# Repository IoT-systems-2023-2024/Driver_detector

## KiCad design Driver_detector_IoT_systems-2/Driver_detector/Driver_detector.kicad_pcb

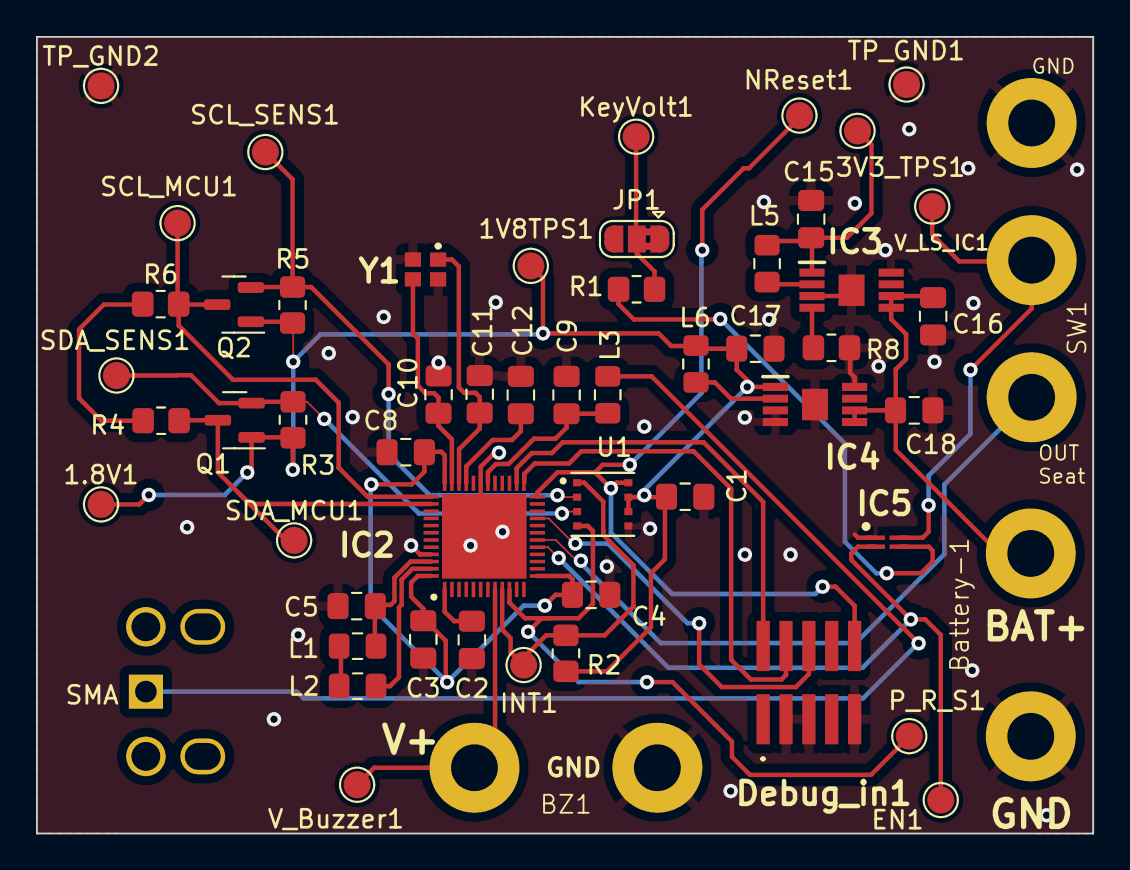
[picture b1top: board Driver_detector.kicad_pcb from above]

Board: 2 copper layers, 58.7 x 44.3 mm, 56 parts (0 on the bottom side), 34 nets.

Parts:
1.8V1, 1V8TPS1, 3V3_TPS1: TestPoint; TestPoint_Pad_D1.5mm
AE1: Antenna; SMA-connector
BZ1: Buzzer; Battery_pad
Battery-1: Battery+; Battery_pad
C1: 0.1 nF; C_0805_2012Metric_Pad1.18x1.45mm_HandSolder
C2, C4, C8: 100nF; C_0805_2012Metric_Pad1.18x1.45mm_HandSolder
C3, C16, C18: 4.7uF; C_0805_2012Metric_Pad1.18x1.45mm_HandSolder
C5: 1uF; C_0805_2012Metric_Pad1.18x1.45mm_HandSolder
C9: 0.8pF; C_0805_2012Metric_Pad1.18x1.45mm_HandSolder
C10, C11: 12pF; C_0805_2012Metric_Pad1.18x1.45mm_HandSolder
C12: 100pF; C_0805_2012Metric_Pad1.18x1.45mm_HandSolder
C15, C17: 10uF; C_0805_2012Metric_Pad1.18x1.45mm_HandSolder
Debug_in1: Pin header 2x5, 1.27mm; FTSH10501LDVK
EN1: TestPoint; TestPoint_Pad_D1.5mm
IC2: NRF52832-QFAA-G-R7; QFN40P600X600X95-49N
IC3, IC4: TPS62842DGR; SOP65P490X110-9N
IC5: LS0504EDD12; SON50P160X120X60-4N
INT1: TestPoint; TestPoint_Pad_D1.5mm
JP1: Jumper_2_Bridged; SolderJumper-3_P1.3mm_Bridged2Bar12_RoundedPad1.0x1.5mm
KeyVolt1: TestPoint; TestPoint_Pad_D1.5mm
L1: 15nH; L_0805_2012Metric_Pad1.15x1.40mm_HandSolder
L2: 10uH; L_0805_2012Metric_Pad1.15x1.40mm_HandSolder
L3: 3.9nH; L_0805_2012Metric_Pad1.15x1.40mm_HandSolder
L5, L6: 2.2uH; L_0805_2012Metric_Pad1.15x1.40mm_HandSolder
NReset1: TestPoint; TestPoint_Pad_D1.5mm
P_R_S1: TestPoint; TestPoint_Pad_D1.5mm
Q1, Q2: BSS138; SOT-23
R1: OR; R_0805_2012Metric_Pad1.20x1.40mm_HandSolder
R2, R3, R4, R5, R6: 10k; R_0805_2012Metric_Pad1.20x1.40mm_HandSolder
R8: 52.3kOhm; R_0805_2012Metric_Pad1.20x1.40mm_HandSolder
SCL_MCU1: TestPoint; TestPoint_Pad_D1.5mm
SCL_SENS1: TestPoint; TestPoint_Pad_D1.5mm
SDA_MCU1: TestPoint; TestPoint_Pad_D1.5mm
SDA_SENS1: TestPoint; TestPoint_Pad_D1.5mm
SW1: SW_SPDT; Footprint_switch
TP_GND1, TP_GND2: TestPoint; TestPoint_Pad_D1.5mm
U1: CH-101; XDCR_CH-101
V_Buzzer1: TestPoint; TestPoint_Pad_D1.5mm
V_LS_IC1: TestPoint; TestPoint_Pad_D1.5mm
Y1: CX2016DB32000D0FLJCC

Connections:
+1V8: 1.8V1.1, 1V8TPS1.1, C1.2, C17.1, IC4.1 (VOS), L6.1, Q1.1 (G), Q2.1 (G), R2.1, R3.1, R5.1, U1.6 (VDD), U1.7 (AVDD)
+3.3V: R4.1, R6.1
Battery +: Battery-1.2, C16.1, C18.1, IC3.5 (EN), IC3.6 (VIN), IC4.5 (EN), IC4.6 (VIN)
EN: EN1.1, IC2.17 (P0.14/TRACEDATA[3]), IC5.2 (EN)
GND: BZ1.2 (+), Battery-1.1, C1.1, C2.1, C3.2, C4.2, C5.2, C8.2, C9.2, C10.2, C11.1, C12.1, C15.2, C16.2, C17.2, C18.2, Debug_in1.3, Debug_in1.5, Debug_in1.9, IC2.31 (VSS_1), IC2.45 (VSS_2), IC2.49 (EP), IC3.3 (MODE), IC3.8 (GND), IC3.9 (EP), IC4.3 (MODE), IC4.4 (VSET), IC4.8 (GND), IC4.9 (EP), IC5.1 (GND), R8.2, SW1.1 (A), TP_GND1.1, TP_GND2.1, U1.5 (VSS), Y1.2 (GND_1), Y1.4 (GND_2)
INT: IC2.9 (P0.07), INT1.1, R2.2, U1.1 (INT)
NRESET: Debug_in1.10, IC2.24 (P0.21/NRESET), NReset1.1, U1.8 (~RESET)
unnamed: AE1.1 (A), L3.2
unnamed: C9.1, IC2.30 (ANT), L3.1
unnamed: IC2.47 (DCC), L2.2
unnamed: C2.2, IC2.1 (DEC1)
unnamed: C12.2, IC2.33 (DEC3)
unnamed: C5.1, IC2.46 (DEC4), L1.1
unnamed: C11.2, IC2.34 (XC1), Y1.1 (HOT_1)
unnamed: C10.1, IC2.35 (XC2), Y1.3 (HOT_2)
unnamed: IC3.2 (SW), L5.2
unnamed: 3V3_TPS1.1, C15.1, IC3.1 (VOS), L5.1
unnamed: IC3.4 (VSET), R8.1
unnamed: IC4.2 (SW), L6.2
unnamed: IC5.3 (IN), R1.2
unnamed: IC5.4 (OUT), SW1.3 (C), V_LS_IC1.1
unnamed: JP1.2 (B), KeyVolt1.1, R1.1
unnamed: L1.2, L2.1
Output_seatbelt: IC2.18 (P0.15/TRACEDATA[2]), SW1.2 (B)
Pro_range_sens: IC2.10 (P0.08), P_R_S1.1, U1.4 (PROG)
SCL_MCU: IC2.37 (P0.25), Q2.3 (D), R6.2, SCL_MCU1.1
SCL_Sens: Q2.2 (S), R5.2, SCL_SENS1.1, U1.2 (SCL)
SDA_MCU: IC2.38 (P0.26), Q1.3 (D), R4.2, SDA_MCU1.1
SDA_Sens: Q1.2 (S), R3.2, SDA_SENS1.1, U1.3 (SDA)
SWDCLK: Debug_in1.4, IC2.25 (SWDCLK)
SWDIO: Debug_in1.2, IC2.26 (SWDIO)
SWO: Debug_in1.6, IC2.21 (P0.18/TRACEDATA[0]/SWO)
VDD: C3.1, C4.1, C8.1, IC2.13 (VDD_1), IC2.36 (VDD_2), IC2.48 (VDD_3)
Voltage_buzzer: BZ1.1 (-), IC2.8 (P0.06), V_Buzzer1.1

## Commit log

2023-11-29 Laatste versie
2023-12-01 code ble + ch101
2023-12-06 code zou moeten werken
2023-12-11 fix ch101
2023-12-13 button bluetooth
2023-12-21 einde
